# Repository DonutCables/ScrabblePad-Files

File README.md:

# ScrabblePad

 "scrabblepad.xxx" = Default files using the GB pinout and setup. 
 Alternate files:
	scrabblepad - 6mil_traces - Base board with routed switch and diode matrix, no other components placed. 
	scrabblepad - centered controller - Same pinout and schematic as the GB board before I remembered there were centered standoffs in the JOlimon case. 
	
SVG/DXF files: width should be 285.75mm 

An assembly guide can be found at https://github.com/JonasGe/ScrabblepadAssembly

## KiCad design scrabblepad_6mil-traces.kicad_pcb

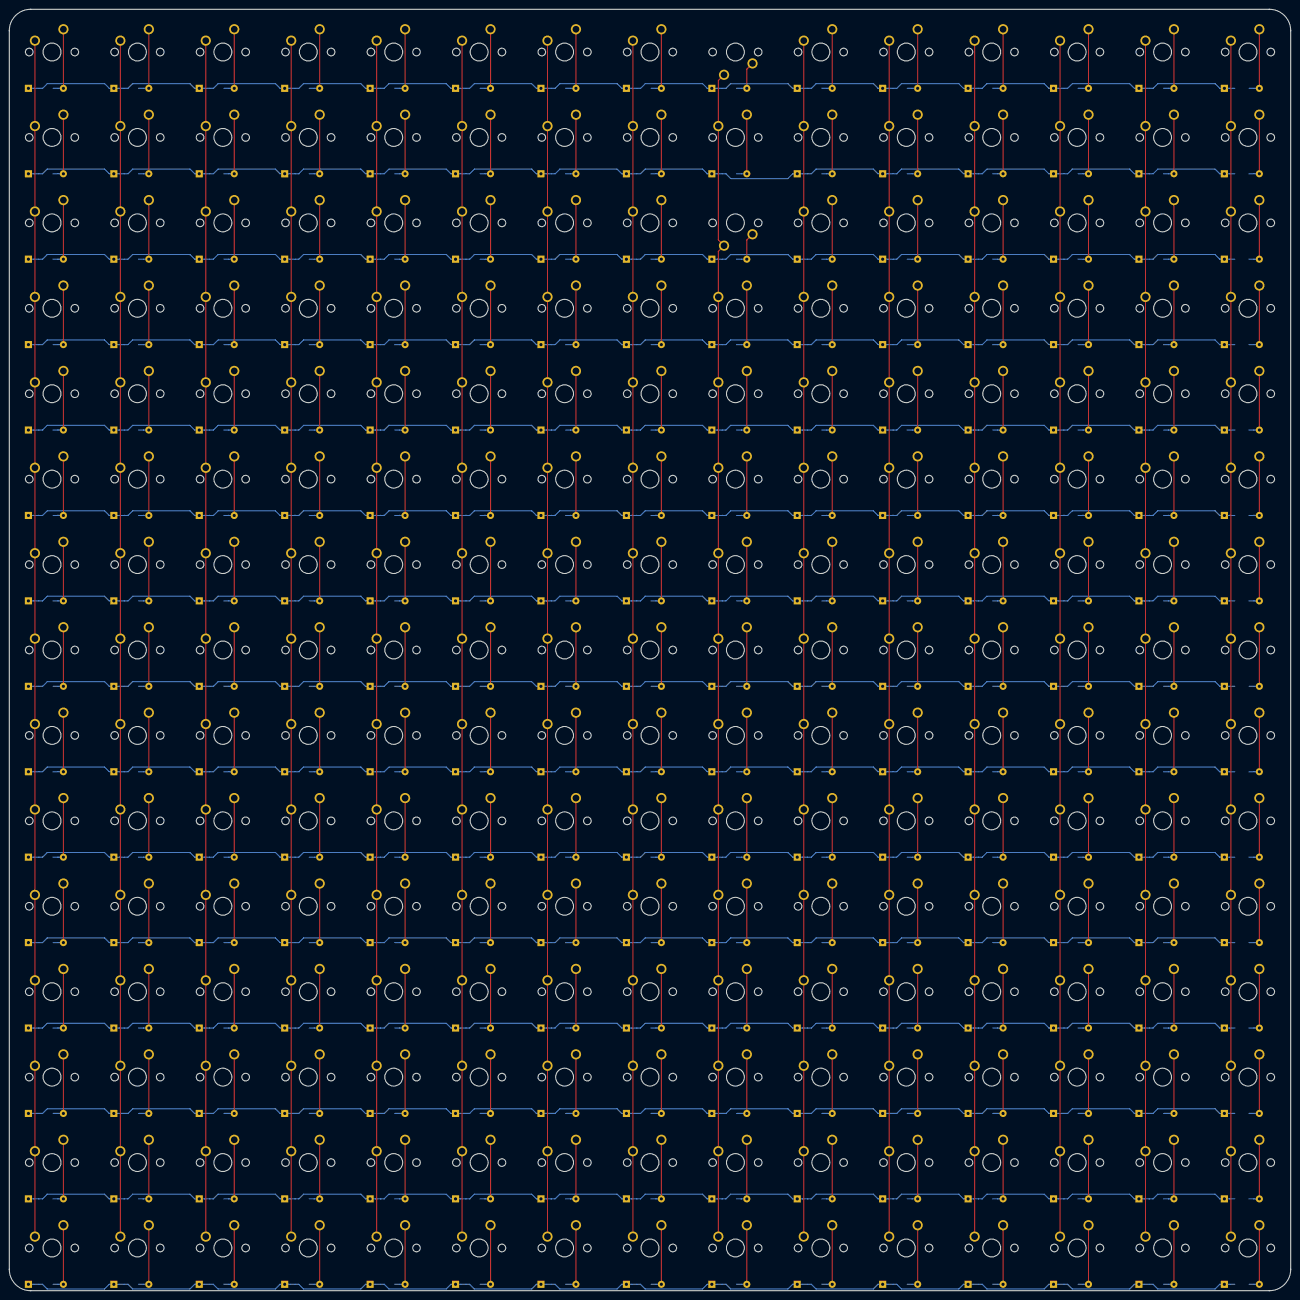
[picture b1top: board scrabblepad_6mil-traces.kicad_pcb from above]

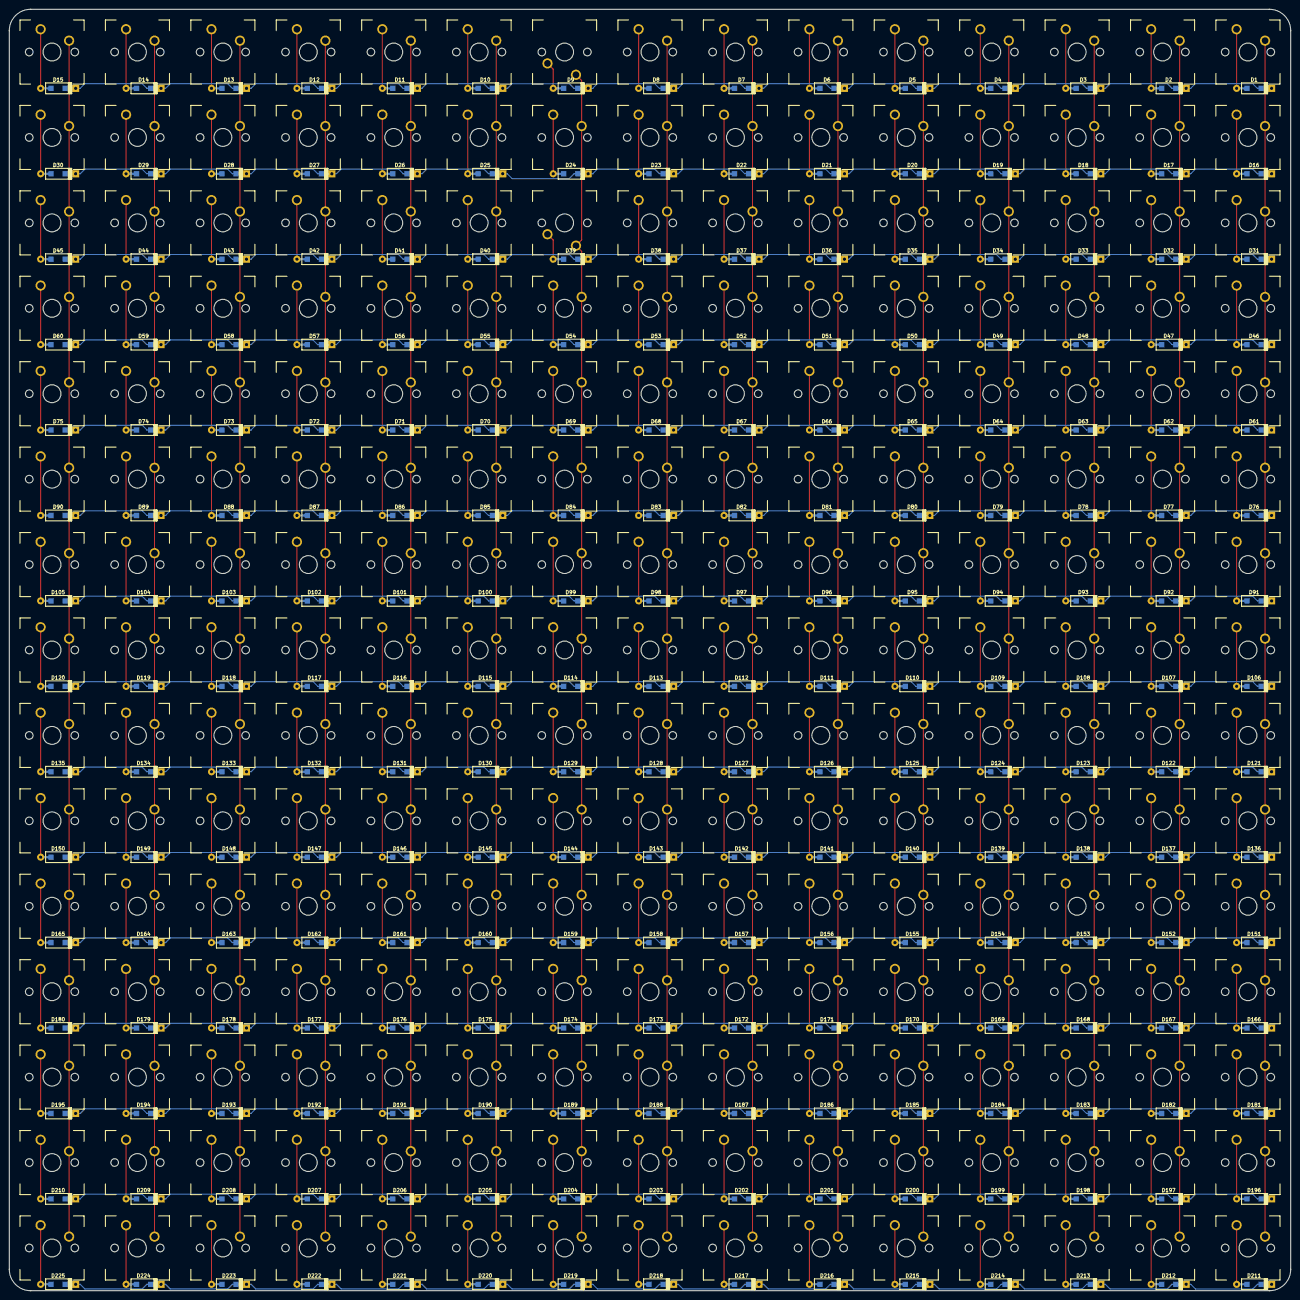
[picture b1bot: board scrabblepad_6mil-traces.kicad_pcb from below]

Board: 2 copper layers, 285.8 x 285.8 mm, 450 parts (225 on the bottom side), 255 nets.

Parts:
D1, D2, D3, D4, D5, D6, D7, D8, D9, D10, D11, D12, D13, D14, D15, D16, D17, D18, D19, D20, D21, D22, D23, D24, D25, D26, D27, D28, D29, D30, D31, D32, D33, D34, D35, D36, D37, D38, D39, D40, D41, D42, D43, D44, D45, D46, D47, D48, D49, D50, D51, D52, D53, D54, D55, D56, D57, D58, D59, D60, D61, D62, D63, D64, D65, D66, D67, D68, D69, D70, D71, D72, D73, D74, D75, D76, D77, D78, D79, D80, D81, D82, D83, D84, D85, D86, D87, D88, D89, D90, D91, D92, D93, D94, D95, D96, D97, D98, D99, D100, D101, D102, D103, D104, D105, D106, D107, D108, D109, D110, D111, D112, D113, D114, D115, D116, D117, D118, D119, D120, D121, D122, D123, D124, D125, D126, D127, D128, D129, D130, D131, D132, D133, D134, D135, D136, D137, D138, D139, D140, D141, D142, D143, D144, D145, D146, D147, D148, D149, D150, D151, D152, D153, D154, D155, D156, D157, D158, D159, D160, D161, D162, D163, D164, D165, D166, D167, D168, D169, D170, D171, D172, D173, D174, D175, D176, D177, D178, D179, D180, D181, D182, D183, D184, D185, D186, D187, D188, D189, D190, D191, D192, D193, D194, D195, D196, D197, D198, D199, D200, D201, D202, D203, D204, D205, D206, D207, D208, D209, D210, D211, D212, D213, D214, D215, D216, D217, D218, D219, D220, D221, D222, D223, D224, D225: D; D_SOD123_axial
SW_1, SW_2, SW_3, SW_4, SW_5, SW_6, SW_7, SW_8, SW_9, SW_10, SW_11, SW_12, SW_13, SW_14, SW_15, SW_16, SW_17, SW_18, SW_19, SW_20, SW_21, SW_22, SW_23, SW_24, SW_25, SW_26, SW_27, SW_28, SW_29, SW_30, SW_31, SW_32, SW_33, SW_34, SW_35, SW_36, SW_37, SW_38, SW_39, SW_40, SW_41, SW_42, SW_43, SW_44, SW_45, SW_46, SW_47, SW_48, SW_49, SW_50, SW_51, SW_52, SW_53, SW_54, SW_55, SW_56, SW_57, SW_58, SW_59, SW_60, SW_61, SW_62, SW_63, SW_64, SW_65, SW_66, SW_67, SW_68, SW_69, SW_70, SW_71, SW_72, SW_73, SW_74, SW_75, SW_76, SW_77, SW_78, SW_79, SW_80, SW_81, SW_82, SW_83, SW_84, SW_85, SW_86, SW_87, SW_88, SW_89, SW_90, SW_91, SW_92, SW_93, SW_94, SW_95, SW_96, SW_97, SW_98, SW_99, SW_100, SW_101, SW_102, SW_103, SW_104, SW_105, SW_106, SW_107, SW_108, SW_109, SW_110, SW_111, SW_112, SW_113, SW_114, SW_115, SW_116, SW_117, SW_118, SW_119, SW_120, SW_121, SW_122, SW_123, SW_124, SW_125, SW_126, SW_127, SW_128, SW_129, SW_130, SW_131, SW_132, SW_133, SW_134, SW_135, SW_136, SW_137, SW_138, SW_139, SW_140, SW_141, SW_142, SW_143, SW_144, SW_145, SW_146, SW_147, SW_148, SW_149, SW_150, SW_151, SW_152, SW_153, SW_154, SW_155, SW_156, SW_157, SW_158, SW_159, SW_160, SW_161, SW_162, SW_163, SW_164, SW_165, SW_166, SW_167, SW_168, SW_169, SW_170, SW_171, SW_172, SW_173, SW_174, SW_175, SW_176, SW_177, SW_178, SW_179, SW_180, SW_181, SW_182, SW_183, SW_184, SW_185, SW_186, SW_187, SW_188, SW_189, SW_190, SW_191, SW_192, SW_193, SW_194, SW_195, SW_196, SW_197, SW_198, SW_199, SW_200, SW_201, SW_202, SW_203, SW_204, SW_205, SW_206, SW_207, SW_208, SW_209, SW_210, SW_211, SW_212, SW_213, SW_214, SW_215, SW_216, SW_217, SW_218, SW_219, SW_220, SW_221, SW_222, SW_223, SW_224, SW_225: MX_LED; MX_PCB_SW

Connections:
/Col0: SW_1.SW1, SW_16.SW1, SW_31.SW1, SW_46.SW1, SW_61.SW1, SW_76.SW1, SW_91.SW1, SW_106.SW1, SW_121.SW1, SW_136.SW1, SW_151.SW1, SW_166.SW1, SW_181.SW1, SW_196.SW1, SW_211.SW1
/Col1: SW_2.SW1, SW_17.SW1, SW_32.SW1, SW_47.SW1, SW_62.SW1, SW_77.SW1, SW_92.SW1, SW_107.SW1, SW_122.SW1, SW_137.SW1, SW_152.SW1, SW_167.SW1, SW_182.SW1, SW_197.SW1, SW_212.SW1
/Col2: SW_3.SW1, SW_18.SW1, SW_33.SW1, SW_48.SW1, SW_63.SW1, SW_78.SW1, SW_93.SW1, SW_108.SW1, SW_123.SW1, SW_138.SW1, SW_153.SW1, SW_168.SW1, SW_183.SW1, SW_198.SW1, SW_213.SW1
/Col3: SW_4.SW1, SW_19.SW1, SW_34.SW1, SW_49.SW1, SW_64.SW1, SW_79.SW1, SW_94.SW1, SW_109.SW1, SW_124.SW1, SW_139.SW1, SW_154.SW1, SW_169.SW1, SW_184.SW1, SW_199.SW1, SW_214.SW1
/Col4: SW_5.SW1, SW_20.SW1, SW_35.SW1, SW_50.SW1, SW_65.SW1, SW_80.SW1, SW_95.SW1, SW_110.SW1, SW_125.SW1, SW_140.SW1, SW_155.SW1, SW_170.SW1, SW_185.SW1, SW_200.SW1, SW_215.SW1
/Col5: SW_6.SW1, SW_21.SW1, SW_36.SW1, SW_51.SW1, SW_66.SW1, SW_81.SW1, SW_96.SW1, SW_111.SW1, SW_126.SW1, SW_141.SW1, SW_156.SW1, SW_171.SW1, SW_186.SW1, SW_201.SW1, SW_216.SW1
/Col6: SW_7.SW1, SW_22.SW1, SW_37.SW1, SW_52.SW1, SW_67.SW1, SW_82.SW1, SW_97.SW1, SW_112.SW1, SW_127.SW1, SW_142.SW1, SW_157.SW1, SW_172.SW1, SW_187.SW1, SW_202.SW1, SW_217.SW1
/Col7: SW_8.SW1, SW_23.SW1, SW_38.SW1, SW_53.SW1, SW_68.SW1, SW_83.SW1, SW_98.SW1, SW_113.SW1, SW_128.SW1, SW_143.SW1, SW_158.SW1, SW_173.SW1, SW_188.SW1, SW_203.SW1, SW_218.SW1
/Col8: SW_9.SW2, SW_24.SW1, SW_39.SW2, SW_54.SW1, SW_69.SW1, SW_84.SW1, SW_99.SW1, SW_114.SW1, SW_129.SW1, SW_144.SW1, SW_159.SW1, SW_174.SW1, SW_189.SW1, SW_204.SW1, SW_219.SW1
/Col9: SW_10.SW1, SW_25.SW1, SW_40.SW1, SW_55.SW1, SW_70.SW1, SW_85.SW1, SW_100.SW1, SW_115.SW1, SW_130.SW1, SW_145.SW1, SW_160.SW1, SW_175.SW1, SW_190.SW1, SW_205.SW1, SW_220.SW1
/Col10: SW_11.SW1, SW_26.SW1, SW_41.SW1, SW_56.SW1, SW_71.SW1, SW_86.SW1, SW_101.SW1, SW_116.SW1, SW_131.SW1, SW_146.SW1, SW_161.SW1, SW_176.SW1, SW_191.SW1, SW_206.SW1, SW_221.SW1
/Col11: SW_12.SW1, SW_27.SW1, SW_42.SW1, SW_57.SW1, SW_72.SW1, SW_87.SW1, SW_102.SW1, SW_117.SW1, SW_132.SW1, SW_147.SW1, SW_162.SW1, SW_177.SW1, SW_192.SW1, SW_207.SW1, SW_222.SW1
/Col12: SW_13.SW1, SW_28.SW1, SW_43.SW1, SW_58.SW1, SW_73.SW1, SW_88.SW1, SW_103.SW1, SW_118.SW1, SW_133.SW1, SW_148.SW1, SW_163.SW1, SW_178.SW1, SW_193.SW1, SW_208.SW1, SW_223.SW1
/Col13: SW_14.SW1, SW_29.SW1, SW_44.SW1, SW_59.SW1, SW_74.SW1, SW_89.SW1, SW_104.SW1, SW_119.SW1, SW_134.SW1, SW_149.SW1, SW_164.SW1, SW_179.SW1, SW_194.SW1, SW_209.SW1, SW_224.SW1
/Col14: SW_15.SW1, SW_30.SW1, SW_45.SW1, SW_60.SW1, SW_75.SW1, SW_90.SW1, SW_105.SW1, SW_120.SW1, SW_135.SW1, SW_150.SW1, SW_165.SW1, SW_180.SW1, SW_195.SW1, SW_210.SW1, SW_225.SW1
/Row0: D1.1, D2.1, D3.1, D4.1, D5.1, D6.1, D7.1, D8.1, D9.1, D10.1, D11.1, D12.1, D13.1, D14.1, D15.1
/Row1: D16.1, D17.1, D18.1, D19.1, D20.1, D21.1, D22.1, D23.1, D24.1, D25.1, D26.1, D27.1, D28.1, D29.1, D30.1
/Row2: D31.1, D32.1, D33.1, D34.1, D35.1, D36.1, D37.1, D38.1, D39.1, D40.1, D41.1, D42.1, D43.1, D44.1, D45.1
/Row3: D46.1, D47.1, D48.1, D49.1, D50.1, D51.1, D52.1, D53.1, D54.1, D55.1, D56.1, D57.1, D58.1, D59.1, D60.1
/Row4: D61.1, D62.1, D63.1, D64.1, D65.1, D66.1, D67.1, D68.1, D69.1, D70.1, D71.1, D72.1, D73.1, D74.1, D75.1
/Row5: D76.1, D77.1, D78.1, D79.1, D80.1, D81.1, D82.1, D83.1, D84.1, D85.1, D86.1, D87.1, D88.1, D89.1, D90.1
/Row6: D91.1, D92.1, D93.1, D94.1, D95.1, D96.1, D97.1, D98.1, D99.1, D100.1, D101.1, D102.1, D103.1, D104.1, D105.1
/Row7: D106.1, D107.1, D108.1, D109.1, D110.1, D111.1, D112.1, D113.1, D114.1, D115.1, D116.1, D117.1, D118.1, D119.1, D120.1
/Row8: D121.1, D122.1, D123.1, D124.1, D125.1, D126.1, D127.1, D128.1, D129.1, D130.1, D131.1, D132.1, D133.1, D134.1, D135.1
/Row9: D136.1, D137.1, D138.1, D139.1, D140.1, D141.1, D142.1, D143.1, D144.1, D145.1, D146.1, D147.1, D148.1, D149.1, D150.1
/Row10: D151.1, D152.1, D153.1, D154.1, D155.1, D156.1, D157.1, D158.1, D159.1, D160.1, D161.1, D162.1, D163.1, D164.1, D165.1
/Row11: D166.1, D167.1, D168.1, D169.1, D170.1, D171.1, D172.1, D173.1, D174.1, D175.1, D176.1, D177.1, D178.1, D179.1, D180.1
/Row12: D181.1, D182.1, D183.1, D184.1, D185.1, D186.1, D187.1, D188.1, D189.1, D190.1, D191.1, D192.1, D193.1, D194.1, D195.1
/Row13: D196.1, D197.1, D198.1, D199.1, D200.1, D201.1, D202.1, D203.1, D204.1, D205.1, D206.1, D207.1, D208.1, D209.1, D210.1
/Row14: D211.1, D212.1, D213.1, D214.1, D215.1, D216.1, D217.1, D218.1, D219.1, D220.1, D221.1, D222.1, D223.1, D224.1, D225.1
unnamed: D1.2, SW_1.SW2
unnamed: D2.2, SW_2.SW2
unnamed: D3.2, SW_3.SW2
unnamed: D4.2, SW_4.SW2
unnamed: D5.2, SW_5.SW2
unnamed: D6.2, SW_6.SW2
unnamed: D7.2, SW_7.SW2
unnamed: D8.2, SW_8.SW2
unnamed: D9.2, SW_9.SW1
unnamed: D10.2, SW_10.SW2
unnamed: D11.2, SW_11.SW2
unnamed: D12.2, SW_12.SW2
unnamed: D13.2, SW_13.SW2
unnamed: D14.2, SW_14.SW2
unnamed: D15.2, SW_15.SW2
unnamed: D16.2, SW_16.SW2
unnamed: D17.2, SW_17.SW2
unnamed: D18.2, SW_18.SW2
unnamed: D19.2, SW_19.SW2
unnamed: D20.2, SW_20.SW2
unnamed: D21.2, SW_21.SW2
unnamed: D22.2, SW_22.SW2
unnamed: D23.2, SW_23.SW2
unnamed: D24.2, SW_24.SW2
unnamed: D25.2, SW_25.SW2
unnamed: D26.2, SW_26.SW2
unnamed: D27.2, SW_27.SW2
unnamed: D28.2, SW_28.SW2
unnamed: D29.2, SW_29.SW2
unnamed: D30.2, SW_30.SW2
unnamed: D31.2, SW_31.SW2
unnamed: D32.2, SW_32.SW2
unnamed: D33.2, SW_33.SW2
unnamed: D34.2, SW_34.SW2
unnamed: D35.2, SW_35.SW2
unnamed: D36.2, SW_36.SW2
unnamed: D37.2, SW_37.SW2
unnamed: D38.2, SW_38.SW2
unnamed: D39.2, SW_39.SW1
unnamed: D40.2, SW_40.SW2
unnamed: D41.2, SW_41.SW2
unnamed: D42.2, SW_42.SW2
unnamed: D43.2, SW_43.SW2
unnamed: D44.2, SW_44.SW2
unnamed: D45.2, SW_45.SW2
unnamed: D46.2, SW_46.SW2
unnamed: D47.2, SW_47.SW2
unnamed: D48.2, SW_48.SW2
unnamed: D49.2, SW_49.SW2
unnamed: D50.2, SW_50.SW2
unnamed: D51.2, SW_51.SW2
unnamed: D52.2, SW_52.SW2
unnamed: D53.2, SW_53.SW2
unnamed: D54.2, SW_54.SW2
unnamed: D55.2, SW_55.SW2
unnamed: D56.2, SW_56.SW2
unnamed: D57.2, SW_57.SW2
unnamed: D58.2, SW_58.SW2
unnamed: D59.2, SW_59.SW2
unnamed: D60.2, SW_60.SW2
unnamed: D61.2, SW_61.SW2
unnamed: D62.2, SW_62.SW2
unnamed: D63.2, SW_63.SW2
unnamed: D64.2, SW_64.SW2
unnamed: D65.2, SW_65.SW2
unnamed: D66.2, SW_66.SW2
unnamed: D67.2, SW_67.SW2
unnamed: D68.2, SW_68.SW2
unnamed: D69.2, SW_69.SW2
unnamed: D70.2, SW_70.SW2
unnamed: D71.2, SW_71.SW2
unnamed: D72.2, SW_72.SW2
unnamed: D73.2, SW_73.SW2
unnamed: D74.2, SW_74.SW2
unnamed: D75.2, SW_75.SW2
unnamed: D76.2, SW_76.SW2
unnamed: D77.2, SW_77.SW2
unnamed: D78.2, SW_78.SW2
unnamed: D79.2, SW_79.SW2
unnamed: D80.2, SW_80.SW2
unnamed: D81.2, SW_81.SW2
unnamed: D82.2, SW_82.SW2
unnamed: D83.2, SW_83.SW2
unnamed: D84.2, SW_84.SW2
unnamed: D85.2, SW_85.SW2
unnamed: D86.2, SW_86.SW2
unnamed: D87.2, SW_87.SW2
unnamed: D88.2, SW_88.SW2
unnamed: D89.2, SW_89.SW2
unnamed: D90.2, SW_90.SW2
unnamed: D91.2, SW_91.SW2
unnamed: D92.2, SW_92.SW2
unnamed: D93.2, SW_93.SW2
unnamed: D94.2, SW_94.SW2
unnamed: D95.2, SW_95.SW2
unnamed: D96.2, SW_96.SW2
unnamed: D97.2, SW_97.SW2
unnamed: D98.2, SW_98.SW2
unnamed: D99.2, SW_99.SW2
unnamed: D100.2, SW_100.SW2
unnamed: D101.2, SW_101.SW2
unnamed: D102.2, SW_102.SW2
unnamed: D103.2, SW_103.SW2
unnamed: D104.2, SW_104.SW2
unnamed: D105.2, SW_105.SW2
unnamed: D106.2, SW_106.SW2
unnamed: D107.2, SW_107.SW2
unnamed: D108.2, SW_108.SW2
unnamed: D109.2, SW_109.SW2
unnamed: D110.2, SW_110.SW2
unnamed: D111.2, SW_111.SW2
unnamed: D112.2, SW_112.SW2
unnamed: D113.2, SW_113.SW2
unnamed: D114.2, SW_114.SW2
unnamed: D115.2, SW_115.SW2
unnamed: D116.2, SW_116.SW2
unnamed: D117.2, SW_117.SW2
unnamed: D118.2, SW_118.SW2
unnamed: D119.2, SW_119.SW2
unnamed: D120.2, SW_120.SW2
unnamed: D121.2, SW_121.SW2
unnamed: D122.2, SW_122.SW2
unnamed: D123.2, SW_123.SW2
unnamed: D124.2, SW_124.SW2
unnamed: D125.2, SW_125.SW2
unnamed: D126.2, SW_126.SW2
unnamed: D127.2, SW_127.SW2
unnamed: D128.2, SW_128.SW2
unnamed: D129.2, SW_129.SW2
unnamed: D130.2, SW_130.SW2
unnamed: D131.2, SW_131.SW2
unnamed: D132.2, SW_132.SW2
unnamed: D133.2, SW_133.SW2
unnamed: D134.2, SW_134.SW2
unnamed: D135.2, SW_135.SW2
unnamed: D136.2, SW_136.SW2
unnamed: D137.2, SW_137.SW2
unnamed: D138.2, SW_138.SW2
unnamed: D139.2, SW_139.SW2
unnamed: D140.2, SW_140.SW2
unnamed: D141.2, SW_141.SW2
unnamed: D142.2, SW_142.SW2
unnamed: D143.2, SW_143.SW2
unnamed: D144.2, SW_144.SW2
unnamed: D145.2, SW_145.SW2
unnamed: D146.2, SW_146.SW2
unnamed: D147.2, SW_147.SW2
unnamed: D148.2, SW_148.SW2
unnamed: D149.2, SW_149.SW2
unnamed: D150.2, SW_150.SW2
unnamed: D151.2, SW_151.SW2
unnamed: D152.2, SW_152.SW2
unnamed: D153.2, SW_153.SW2
unnamed: D154.2, SW_154.SW2
unnamed: D155.2, SW_155.SW2
unnamed: D156.2, SW_156.SW2
unnamed: D157.2, SW_157.SW2
unnamed: D158.2, SW_158.SW2
unnamed: D159.2, SW_159.SW2
unnamed: D160.2, SW_160.SW2
unnamed: D161.2, SW_161.SW2
unnamed: D162.2, SW_162.SW2
unnamed: D163.2, SW_163.SW2
unnamed: D164.2, SW_164.SW2
unnamed: D165.2, SW_165.SW2
unnamed: D166.2, SW_166.SW2
unnamed: D167.2, SW_167.SW2
unnamed: D168.2, SW_168.SW2
unnamed: D169.2, SW_169.SW2
unnamed: D170.2, SW_170.SW2
unnamed: D171.2, SW_171.SW2
unnamed: D172.2, SW_172.SW2
unnamed: D173.2, SW_173.SW2
unnamed: D174.2, SW_174.SW2
unnamed: D175.2, SW_175.SW2
unnamed: D176.2, SW_176.SW2
unnamed: D177.2, SW_177.SW2
unnamed: D178.2, SW_178.SW2
unnamed: D179.2, SW_179.SW2
unnamed: D180.2, SW_180.SW2
unnamed: D181.2, SW_181.SW2
unnamed: D182.2, SW_182.SW2
unnamed: D183.2, SW_183.SW2
unnamed: D184.2, SW_184.SW2
unnamed: D185.2, SW_185.SW2
unnamed: D186.2, SW_186.SW2
unnamed: D187.2, SW_187.SW2
unnamed: D188.2, SW_188.SW2
unnamed: D189.2, SW_189.SW2
unnamed: D190.2, SW_190.SW2
unnamed: D191.2, SW_191.SW2
unnamed: D192.2, SW_192.SW2
unnamed: D193.2, SW_193.SW2
unnamed: D194.2, SW_194.SW2
unnamed: D195.2, SW_195.SW2
unnamed: D196.2, SW_196.SW2
unnamed: D197.2, SW_197.SW2
unnamed: D198.2, SW_198.SW2
unnamed: D199.2, SW_199.SW2
unnamed: D200.2, SW_200.SW2
unnamed: D201.2, SW_201.SW2
unnamed: D202.2, SW_202.SW2
unnamed: D203.2, SW_203.SW2
unnamed: D204.2, SW_204.SW2
unnamed: D205.2, SW_205.SW2
unnamed: D206.2, SW_206.SW2
unnamed: D207.2, SW_207.SW2
unnamed: D208.2, SW_208.SW2
unnamed: D209.2, SW_209.SW2
unnamed: D210.2, SW_210.SW2
unnamed: D211.2, SW_211.SW2
unnamed: D212.2, SW_212.SW2
unnamed: D213.2, SW_213.SW2
unnamed: D214.2, SW_214.SW2
unnamed: D215.2, SW_215.SW2
unnamed: D216.2, SW_216.SW2
unnamed: D217.2, SW_217.SW2
unnamed: D218.2, SW_218.SW2
unnamed: D219.2, SW_219.SW2
unnamed: D220.2, SW_220.SW2
unnamed: D221.2, SW_221.SW2
unnamed: D222.2, SW_222.SW2
unnamed: D223.2, SW_223.SW2
unnamed: D224.2, SW_224.SW2
unnamed: D225.2, SW_225.SW2

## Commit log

2019-10-24 cleanup
2019-10-24 deleted files cleanup
2019-10-24 added donutbrary
2019-10-24 updated library settings
2019-10-25 license added
2019-10-28 cleanup, library management
2019-11-29 update/cleanup
2019-12-08 added proto files
2019-12-21 simple plate file
2019-12-21 plate file addon
2020-03-24 structure updates
2020-03-24 rearranging
2020-03-24 rearrange
2020-03-24 submodule cleaning
2020-03-24 cleanup and rearranging
2020-03-24 restructure
2020-03-24 submodule get
2020-03-29 render added
2020-04-02 render update
2020-04-02 submodule update
2020-04-22 submodule pub
2020-04-22 updated case parts for plate files
2022-08-09 rev2 kicad files add as submodule
2022-08-09 module name adjustments
2022-08-09 update to readme for build guide
